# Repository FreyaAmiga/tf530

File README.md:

# TF530

** WARNING THIS IS BETA AT THE MOMENT

This repository contains all the files needed to produce a copy of my accelerator board.

The CPLD Required is a XC9572XL-10VQ64

Everything in this repository is released under the GNU GPLv2. You may create or base commercial PCBs from the work in this repository but you must make the sources for all derivative work available. 

## Firmware / Requirements

  * Xilinx ISE, 14.7 (the final version - other versions may work but this is the one I support)
  * JTAG Adaptor

[For more information visit my channel](https://www.youtube.com/c/TerribleFire)

##License

This project and all the files contained are released under the GNU GPLv2. If you build a modified version of the board you must supply the end user with all the sources (this can be a web link).

##The TerribleFire 530 board (Revision 2)

This board is now in Beta. It may not work in all circumstances but it has been verified to boot AmigaOS 1.3, 2.05 and 3.1 and run various games and desktop apps at 25Mhz. Operation is not guarunteed to be crash free but will work in most "happy path" situations.

I have only verified the HD interface with Compact Flash cards.
I have verified this board boots on Amiga 500 Rev 5, 6a, 8.1a

To buy 10 blank copies of the revision 2 board follow the following link.

http://dirtypcbs.com/store/designer/details/12476/1330/tf530-rev2b-zip

(Terrible Fire gets a $2 "cut" for each order... in reality this is a downpayment on future prototype board orders).

I accept no responsibiltiy for any damage to any equipment that results from the use of this board. IT IS ENTIRELY AT YOUR OWN RISK!

## Installation

Installation is exactly the same as the Kipper2k A508. Refer to http://www.kipper2k.com/a500fastmem.html

You need to connect the OVR and INT2 signals to the A500 header port. 

## What does the board look like

## The BOM 

| Qty | Value           | Device             | Package              | Parts                                                  | Description                   | 
|-----|-----------------|--------------------|----------------------|--------------------------------------------------------|-------------------------------|
| 1   |                 | MC68030RC          | MPGA128              | IC1                                                    | 68xxx PROCESSOR               | 
| 1   |                 | MC68881FN-SOC      | PLCC68-S             | IC2                                                    | 68xxx PROCESSOR               |
| 1   | 10K             | RESISTOR1206       | 1206                 | R3                                                     | Resistors                     |
| 13  | 10uF            | CAP_CERAMIC1206    | 1206                 | C1, C2, C3, C4, C5, C6, C7, C8, C9, C10, C11, C12, C13 | Ceramic Capacitors            | 
| 2   | 47K             | RESISTOR1206       | 1206                 | R1, R2                                                 | Resistors                     | 
| 2   | 74LVC1G17DBV    | 74LVC1G17DBV       | SOT23-5              | IC4, IC5                                               | Single Schmitt-Trigger Buffer | 
| 1   | A500            | JUMPER-2PTH        | 1X02                 | A500                                                   | Jumper                        | 
| 4   | AS7C4096A-12TIN | AS7C4096A-12TCN    | TSOP44-II            | U$1, U$2, U$3, U$4                                     |                               |  
| 1   | AUXPINS         | JUMPER-2PTH        | 1X02                 | AUXPINS                                                | Jumper                        | 
| 1   | BYPASS          | JUMPER-2PTH        | 1X02                 | BYPASS                                                 | Jumper (optional)           | 
| 3   | CAY16-103J4LF   | CAY16-103J4LF      | RESCAXE80P320X160-8N | RN1, RN2, RN3                                          | Res Thick Film Array 10K Ohm  | 
| 1   | CDIS            | JUMPER-2PTH        | 1X02                 | JP5                                                    | Jumper                        |
| 1   | CLOCKSEL        | JUMPER-3PTH        | 1X03                 | JP1                                                    |                               | 
| 1   | EXT5V           | JUMPER-2PTH        | 1X02                 | JP7                                                    | Jumper                        |
| 1   | IDE CONNECTOR   | PINHD-2X20         | 2X20                 | IDE                                                    | PIN HEADER                    |
| 1   | JTAG            | HEADER-1X6ROUND    | 1X06_ROUND           | JTAG                                                   | PIN HEADER                    |
| 1   | LM1117          | V_REG_LM1117SOT223 | SOT223               | U1                                                     | 3.3V Voltage  Regulator LM1117 |
| 1   | MC68000         | MC68000P           | DIL64                | X1                                                     | 68xxx PROCESSOR SOCKET        | 
| 1   | MMUDIS          | JUMPER-2PTH        | 1X02                 | JP3                                                    | Jumper                        | 
| 1   | SPI PORT        | PINHD-2X6          | 2X06                 | SPIPORT                                                | PIN HEADER                    | 
| 1   | X24MHZ          | OSCILLATOR         | OSC_7X5MM            | OSC1                                                   | 24 Mhz llators                   |
| 2   | XC9572XL-10VQ64   | XC9572XL-VQ64      | VQ64                 | XC9572XL(BUS), XC9572XL(RAM)                           |                               |

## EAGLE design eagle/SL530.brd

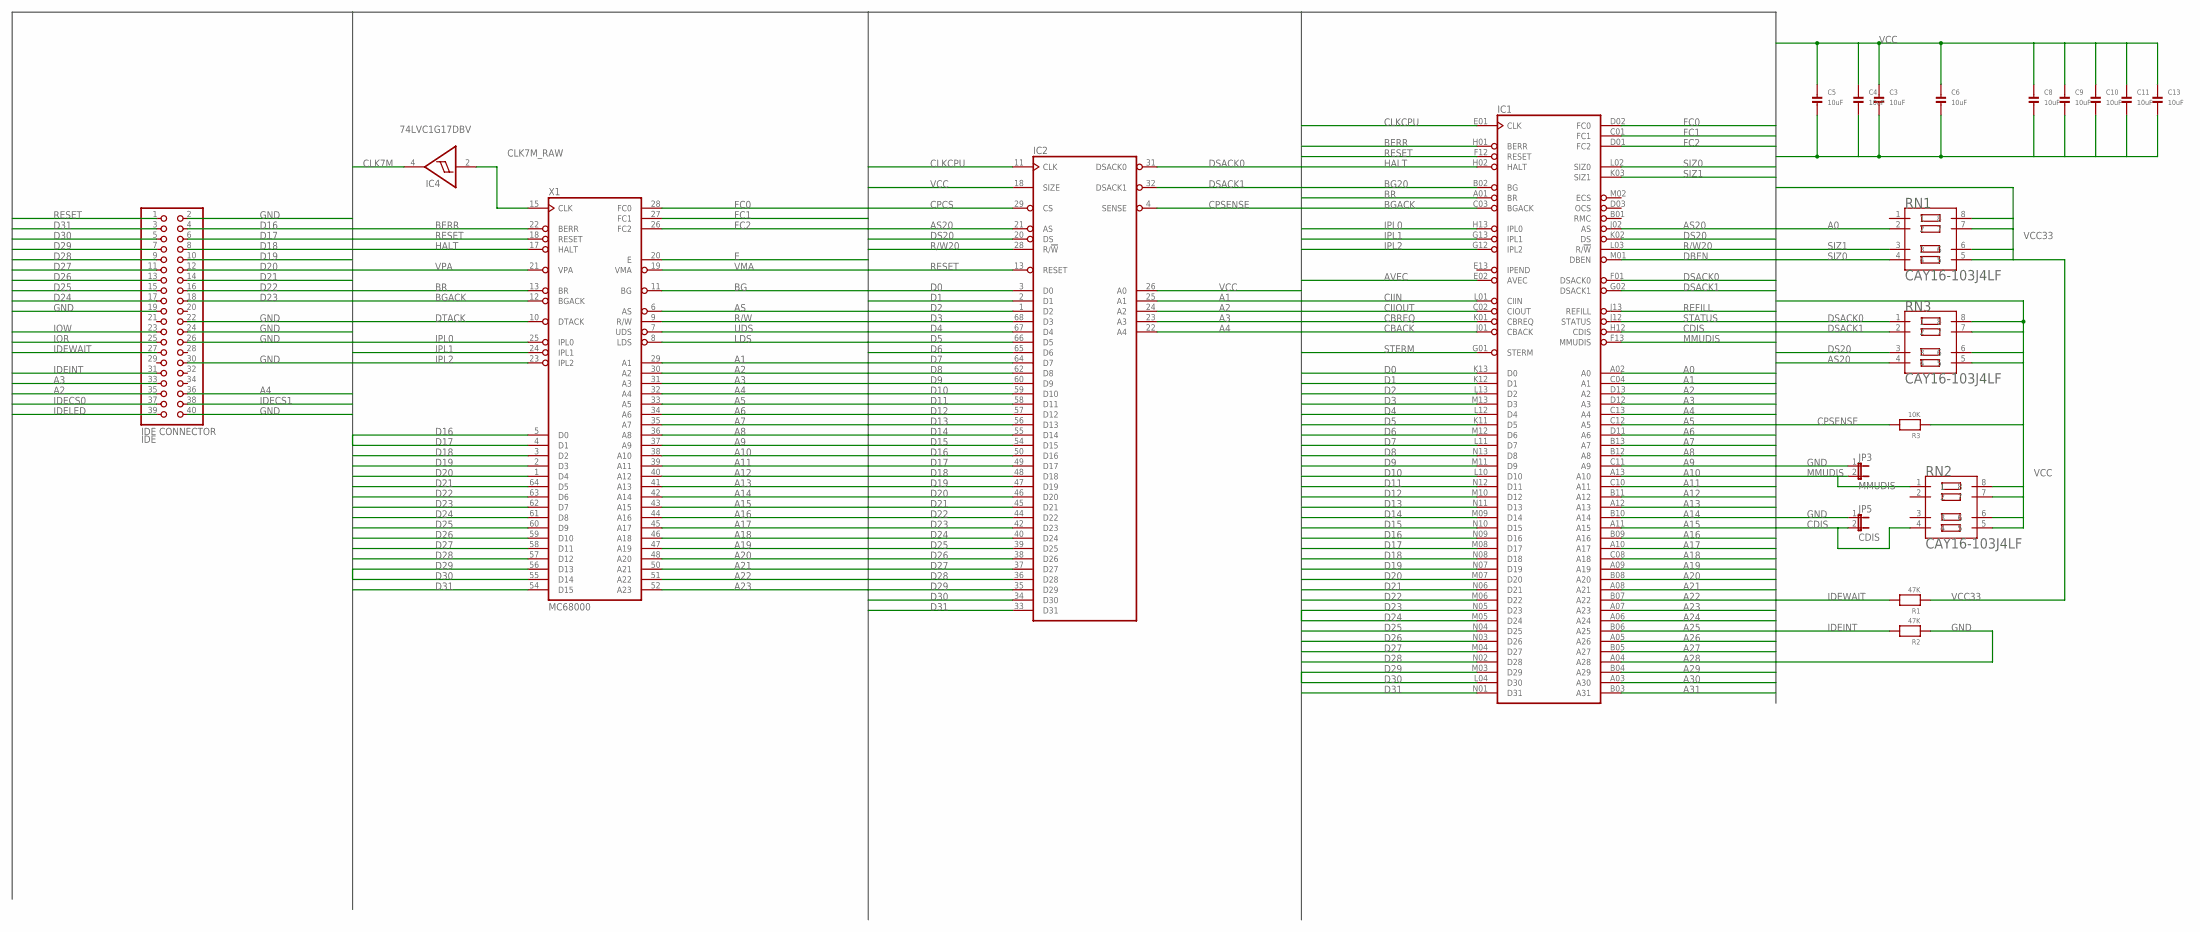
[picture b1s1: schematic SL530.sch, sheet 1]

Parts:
C3, C4, C5, C6, C8, C9, C10, C11, C13: 10uF; 1206
IC1: MC68030RC; MPGA128
IC2: MC68881FN-SOC; PLCC68-S
IC4: 74LVC1G17DBV; SOT23-5
IDE: IDE CONNECTOR; 2X20
JP3: MMUDIS; 1X02
JP5: CDIS; 1X02
R1, R2: 47K; 1206
R3: 10K; 1206
RN1, RN2, RN3: CAY16-103J4LF; RESCAXE80P320X160-8N
X1: MC68000; DIL64

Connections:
A0: IC1.A02 (A0), RN1.2; also elsewhere on the board
A1: IC1.C04 (A1), IC2.25 (A1), X1.29 (A1); also elsewhere on the board
A2: IC1.D13 (A2), IC2.24 (A2), IDE.35, X1.30 (A2); also elsewhere on the board
A3: IC1.D12 (A3), IC2.23 (A3), IDE.33, X1.31 (A3); also elsewhere on the board
A4: IC1.C13 (A4), IC2.22 (A4), IDE.36, X1.32 (A4); also elsewhere on the board
A5: IC1.C12 (A5), X1.33 (A5); also elsewhere on the board
A6: IC1.D11 (A6), X1.34 (A6); also elsewhere on the board
A7: IC1.B13 (A7), X1.35 (A7); also elsewhere on the board
A8: IC1.B12 (A8), X1.36 (A8); also elsewhere on the board
A9: IC1.C11 (A9), X1.37 (A9); also elsewhere on the board
A10: IC1.A13 (A10), X1.38 (A10); also elsewhere on the board
A11: IC1.C10 (A11), X1.39 (A11); also elsewhere on the board
A12: IC1.B11 (A12), X1.40 (A12); also elsewhere on the board
A13: IC1.A12 (A13), X1.41 (A13); also elsewhere on the board
A14: IC1.B10 (A14), X1.42 (A14); also elsewhere on the board
A15: IC1.A11 (A15), X1.43 (A15); also elsewhere on the board
A16: IC1.B09 (A16), X1.44 (A16); also elsewhere on the board
A17: IC1.A10 (A17), X1.45 (A17); also elsewhere on the board
A18: IC1.C08 (A18), X1.46 (A18); also elsewhere on the board
A19: IC1.A09 (A19), X1.47 (A19); also elsewhere on the board
A20: IC1.B08 (A20), X1.48 (A20); also elsewhere on the board
A21: IC1.A08 (A21), X1.50 (A21); also elsewhere on the board
A22: IC1.B07 (A22), X1.51 (A22); also elsewhere on the board
A23: IC1.A07 (A23), X1.52 (A23); also elsewhere on the board
A24: IC1.A06 (A24)
A25: IC1.B06 (A25)
A26: IC1.A05 (A26)
A27: IC1.B05 (A27)
A28: IC1.A04 (A28)
A29: IC1.B04 (A29)
A30: IC1.A03 (A30)
A31: IC1.B03 (A31)
AS: X1.6 (AS); also elsewhere on the board
AS20: IC1.J02 (AS), IC2.21 (AS), RN3.4; also elsewhere on the board
AVEC: IC1.E02 (AVEC); also elsewhere on the board
BERR: IC1.H01 (BERR), X1.22 (BERR); also elsewhere on the board
BG: X1.11 (BG); also elsewhere on the board
BG20: IC1.B02 (BG); also elsewhere on the board
BGACK: IC1.C03 (BGACK), X1.12 (BGACK); also elsewhere on the board
BR: IC1.A01 (BR), X1.13 (BR)
CBACK: IC1.J01 (CBACK); also elsewhere on the board
CBREQ: IC1.K01 (CBREQ); also elsewhere on the board
CDIS: IC1.H12 (CDIS), JP5.2, RN2.4
CIIN: IC1.L01 (CIIN); also elsewhere on the board
CIIOUT: IC1.C02 (CIOUT)
CLK7M: IC4.4 (O); also elsewhere on the board
CLK7M_RAW: IC4.2 (I), X1.15 (CLK)
CLKCPU: IC1.E01 (CLK), IC2.11 (CLK); also elsewhere on the board
CPCS: IC2.29 (CS); also elsewhere on the board
CPSENSE: IC2.4 (SENSE), R3.2; also elsewhere on the board
D0: IC1.K13 (D0), IC2.3 (D0); also elsewhere on the board
D1: IC1.K12 (D1), IC2.2 (D1); also elsewhere on the board
D2: IC1.L13 (D2), IC2.1 (D2); also elsewhere on the board
D3: IC1.M13 (D3), IC2.68 (D3); also elsewhere on the board
D4: IC1.L12 (D4), IC2.67 (D4); also elsewhere on the board
D5: IC1.K11 (D5), IC2.66 (D5); also elsewhere on the board
D6: IC1.M12 (D6), IC2.65 (D6); also elsewhere on the board
D7: IC1.L11 (D7), IC2.64 (D7); also elsewhere on the board
D8: IC1.N13 (D8), IC2.62 (D8); also elsewhere on the board
D9: IC1.M11 (D9), IC2.60 (D9); also elsewhere on the board
D10: IC1.L10 (D10), IC2.59 (D10); also elsewhere on the board
D11: IC1.N12 (D11), IC2.58 (D11); also elsewhere on the board
D12: IC1.M10 (D12), IC2.57 (D12); also elsewhere on the board
D13: IC1.N11 (D13), IC2.56 (D13); also elsewhere on the board
D14: IC1.M09 (D14), IC2.55 (D14); also elsewhere on the board
D15: IC1.N10 (D15), IC2.54 (D15); also elsewhere on the board
D16: IC1.N09 (D16), IC2.50 (D16), IDE.4, X1.5 (D0); also elsewhere on the board
D17: IC1.M08 (D17), IC2.49 (D17), IDE.6, X1.4 (D1); also elsewhere on the board
D18: IC1.N08 (D18), IC2.48 (D18), IDE.8, X1.3 (D2); also elsewhere on the board
D19: IC1.N07 (D19), IC2.47 (D19), IDE.10, X1.2 (D3); also elsewhere on the board
D20: IC1.M07 (D20), IC2.46 (D20), IDE.12, X1.1 (D4); also elsewhere on the board
D21: IC1.N06 (D21), IC2.45 (D21), IDE.14, X1.64 (D5); also elsewhere on the board
D22: IC1.M06 (D22), IC2.44 (D22), IDE.16, X1.63 (D6); also elsewhere on the board
D23: IC1.N05 (D23), IC2.42 (D23), IDE.18, X1.62 (D7); also elsewhere on the board
D24: IC1.M05 (D24), IC2.40 (D24), IDE.17, X1.61 (D8); also elsewhere on the board
D25: IC1.N04 (D25), IC2.39 (D25), IDE.15, X1.60 (D9); also elsewhere on the board
D26: IC1.N03 (D26), IC2.38 (D26), IDE.13, X1.59 (D10); also elsewhere on the board
D27: IC1.M04 (D27), IC2.37 (D27), IDE.11, X1.58 (D11); also elsewhere on the board
D28: IC1.N02 (D28), IC2.36 (D28), IDE.9, X1.57 (D12); also elsewhere on the board
D29: IC1.M03 (D29), IC2.35 (D29), IDE.7, X1.56 (D13); also elsewhere on the board
D30: IC1.L04 (D30), IC2.34 (D30), IDE.5, X1.55 (D14); also elsewhere on the board
D31: IC1.N01 (D31), IC2.33 (D31), IDE.3, X1.54 (D15); also elsewhere on the board
DBEN: IC1.M01 (DBEN)
DS20: IC1.K02 (DS), IC2.20 (DS), RN3.3; also elsewhere on the board
DSACK0: IC1.F01 (DSACK0), IC2.31 (DSACK0), RN3.1; also elsewhere on the board
DSACK1: IC1.G02 (DSACK1), IC2.32 (DSACK1), RN3.2; also elsewhere on the board
DTACK: X1.10 (DTACK); also elsewhere on the board
E: X1.20 (E); also elsewhere on the board
FC0: IC1.D02 (FC0), X1.28 (FC0); also elsewhere on the board
FC1: IC1.C01 (FC1), X1.27 (FC1); also elsewhere on the board
FC2: IC1.D01 (FC2), X1.26 (FC2); also elsewhere on the board
GND: C3.2, C4.2, C5.2, C6.2, C8.2, C9.2, C10.2, C11.2, C13.2, IC1.C05 (GND), IC1.C07 (GND), IC1.C09 (GND), IC1.E03 (GND), IC1.E11 (GND), IC1.F03 (GND), IC1.G03 (GND), IC1.G11 (GND), IC1.J03 (GND), IC1.J11 (GND), IC1.L05 (GND), IC1.L07 (GND), IC1.L08 (GND), IC1.L09 (GND), IC2.5 (GND), IC2.6 (GND), IC2.7 (GND), IC2.8 (GND), IC2.9 (GND), IC2.12 (GND), IC2.14 (GND), IC2.19 (GND), IC2.30 (GND), IC2.41 (GND), IC2.51 (GND), IC2.63 (GND), IC4.3 (GND), IDE.2, IDE.19, IDE.22, IDE.24, IDE.26, IDE.30, IDE.40, JP3.1, JP5.1, R2.1, X1.16 (GND), X1.53 (GND); also elsewhere on the board
HALT: IC1.H02 (HALT), X1.17 (HALT); also elsewhere on the board
IDECS0: IDE.37; also elsewhere on the board
IDECS1: IDE.38; also elsewhere on the board
IDEINT: IDE.31, R2.2; also elsewhere on the board
IDELED: IDE.39
IDEWAIT: IDE.27, R1.2; also elsewhere on the board
IOR: IDE.25; also elsewhere on the board
IOW: IDE.23; also elsewhere on the board
IPL0: IC1.H13 (IPL0), X1.25 (IPL0)
IPL1: IC1.G13 (IPL1), X1.24 (IPL1)
IPL2: IC1.G12 (IPL2), X1.23 (IPL2)
LDS: X1.8 (LDS); also elsewhere on the board
MMUDIS: IC1.F13 (MMUDIS), JP3.2, RN2.1
R/W: X1.9 (R/W); also elsewhere on the board
R/W20: IC1.L03 (R/!W), IC2.28 (R/!W); also elsewhere on the board
REFILL: IC1.J13 (REFILL)
RESET: IC1.F12 (RESET), IC2.13 (RESET), IDE.1, X1.18 (RESET); also elsewhere on the board
SIZ0: IC1.L02 (SIZ0), RN1.4; also elsewhere on the board
SIZ1: IC1.K03 (SIZ1), RN1.3; also elsewhere on the board
STATUS: IC1.J12 (STATUS)
STERM: IC1.G01 (STERM); also elsewhere on the board
UDS: X1.7 (UDS); also elsewhere on the board
VCC: C3.1, C4.1, C5.1, C6.1, C8.1, C9.1, C10.1, C11.1, C13.1, IC1.C06 (VCC), IC1.D04 (VCC), IC1.D10 (VCC), IC1.F02 (VCC), IC1.F11 (VCC), IC1.H03 (VCC), IC1.H11 (VCC), IC1.K04 (VCC), IC1.K10 (VCC), IC1.L06 (VCC), IC2.10 (VCC), IC2.16 (VCC), IC2.17 (VCC), IC2.18 (SIZE), IC2.26 (A0), IC2.27 (VCC), IC2.43 (VCC), IC2.52 (VCC), IC2.53 (VCC), IC2.61 (VCC), IC4.5 (VCC), R3.1, RN2.5, RN2.6, RN2.7, RN2.8, RN3.5, RN3.6, RN3.7, RN3.8, X1.14 (VCC), X1.49 (VCC); also elsewhere on the board
VCC33: R1.1, RN1.5, RN1.6, RN1.7, RN1.8; also elsewhere on the board
VMA: X1.19 (VMA); also elsewhere on the board
VPA: X1.21 (VPA); also elsewhere on the board

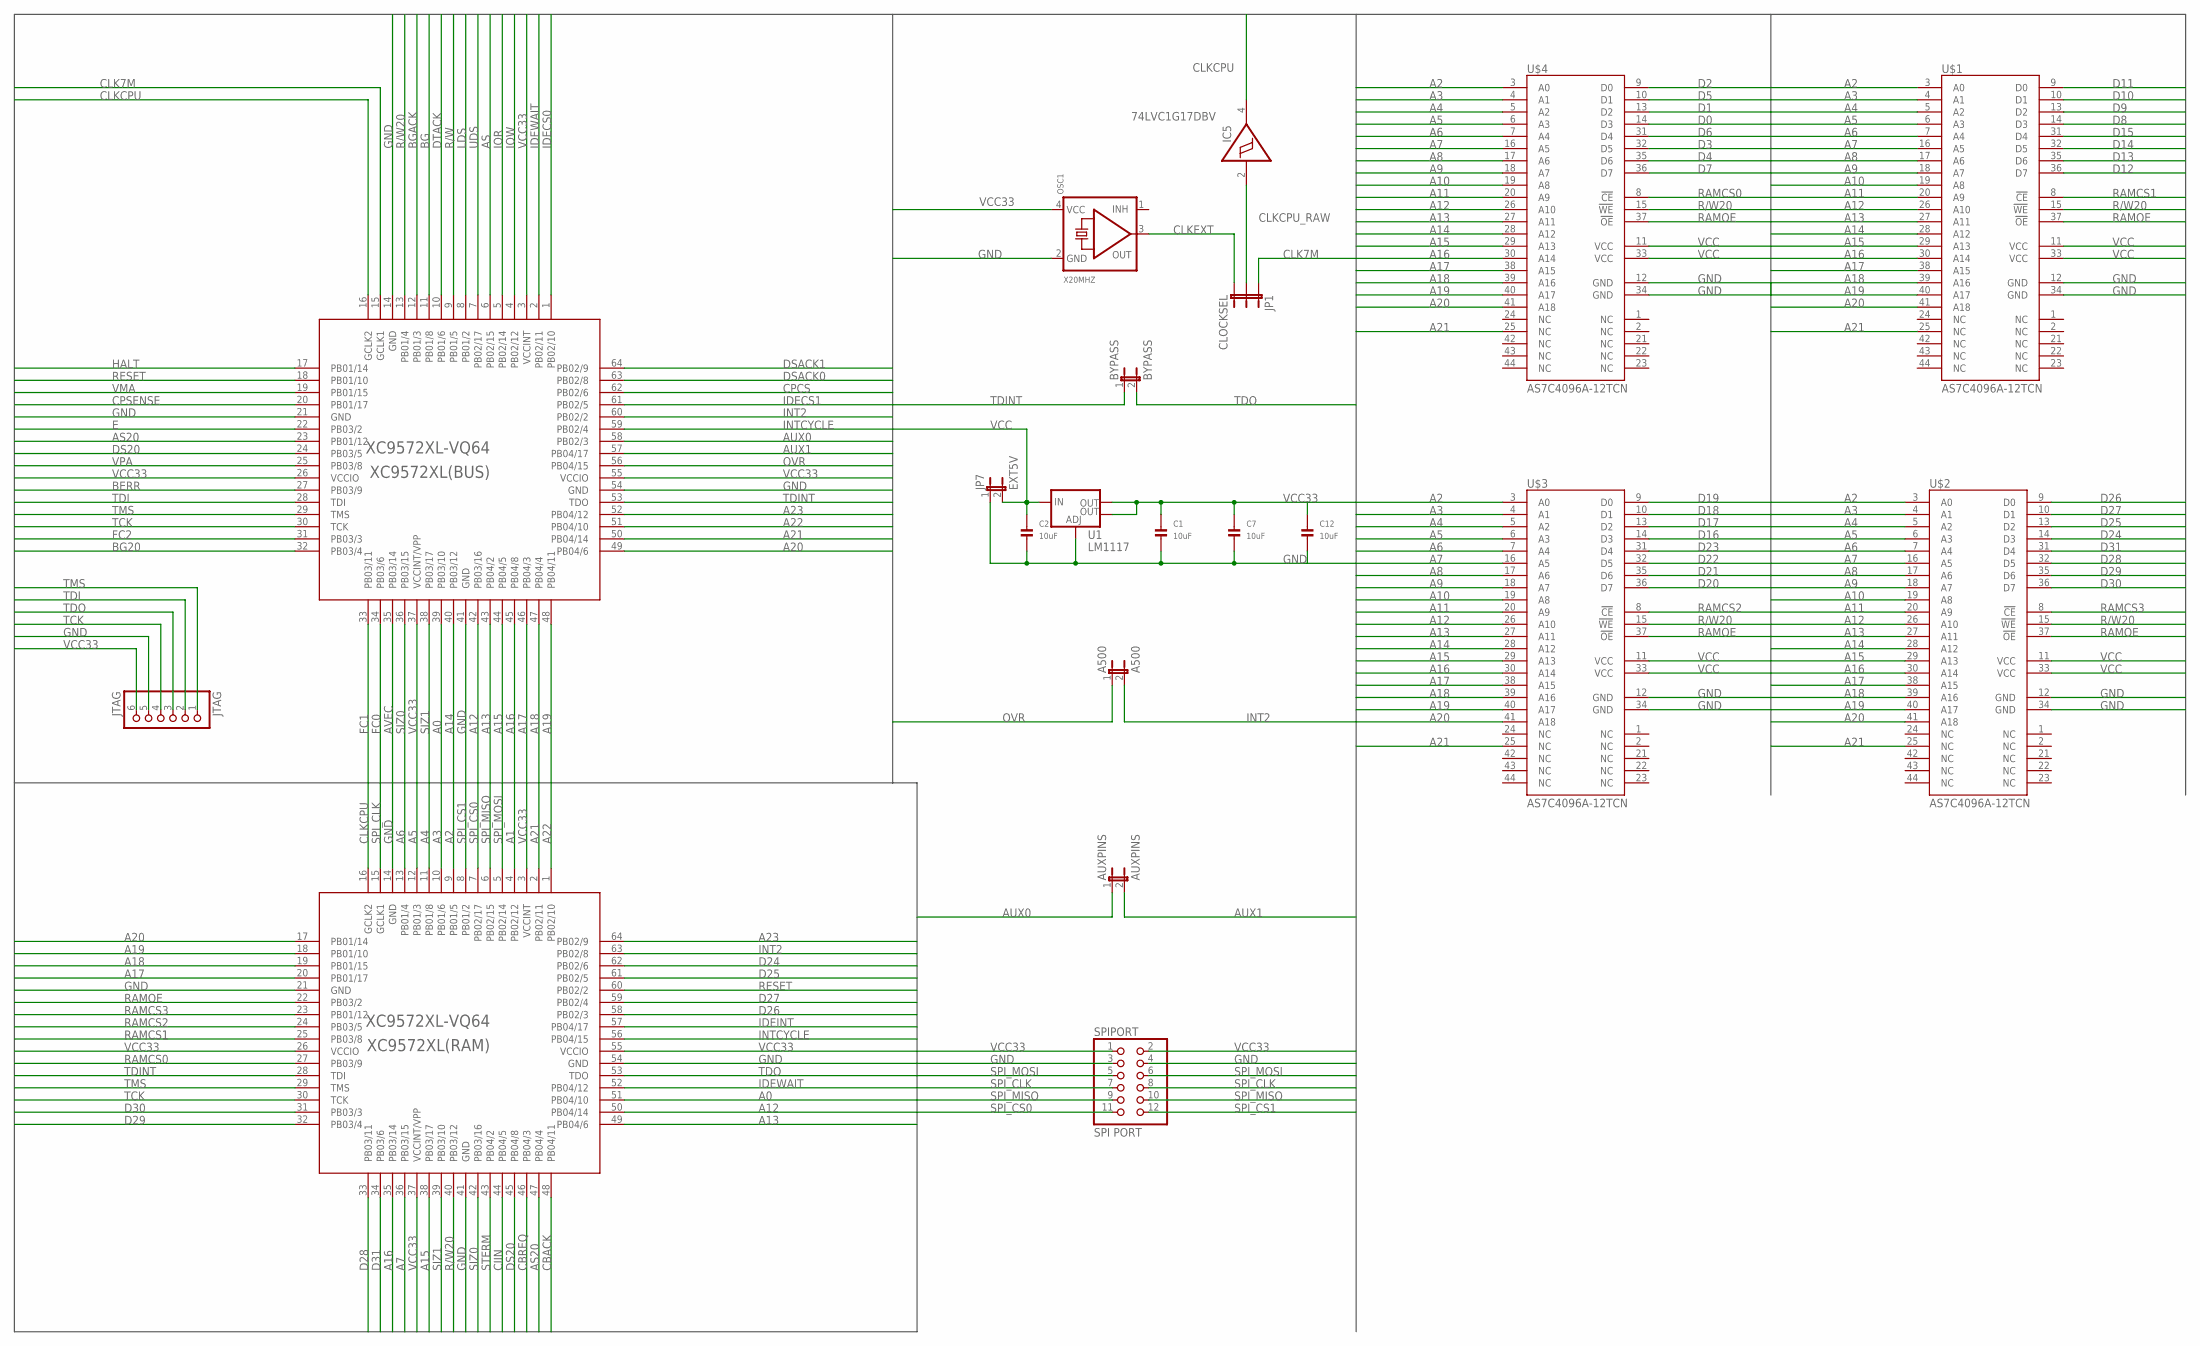
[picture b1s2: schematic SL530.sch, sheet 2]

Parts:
A500: A500; 1X02
AUXPINS: AUXPINS; 1X02
BYPASS: BYPASS; 1X02
C1, C2, C7, C12: 10uF; 1206
IC5: 74LVC1G17DBV; SOT23-5
JP1: CLOCKSEL; 1X03
JP7: EXT5V; 1X02
JTAG: JTAG; 1X06_ROUND
OSC1: X20MHZ; OSC_7X5MM
SPIPORT: SPI PORT; 2X06
U1: LM1117; SOT223
U$1, U$2, U$3, U$4: AS7C4096A-12TCN; TSOP44-II
XC9572XL(BUS), XC9572XL(RAM): XC9572XL-VQ64; VQ64

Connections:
A0: XC9572XL(BUS).39 (PB03/10), XC9572XL(RAM).51 (PB04/10); also elsewhere on the board
A1: XC9572XL(RAM).4 (PB02/12); also elsewhere on the board
A2: U$1.3 (A0), U$2.3 (A0), U$3.3 (A0), U$4.3 (A0), XC9572XL(RAM).9 (PB01/5); also elsewhere on the board
A3: U$1.4 (A1), U$2.4 (A1), U$3.4 (A1), U$4.4 (A1), XC9572XL(RAM).10 (PB01/6); also elsewhere on the board
A4: U$1.5 (A2), U$2.5 (A2), U$3.5 (A2), U$4.5 (A2), XC9572XL(RAM).11 (PB01/8); also elsewhere on the board
A5: U$1.6 (A3), U$2.6 (A3), U$3.6 (A3), U$4.6 (A3), XC9572XL(RAM).12 (PB01/3); also elsewhere on the board
A6: U$1.7 (A4), U$2.7 (A4), U$3.7 (A4), U$4.7 (A4), XC9572XL(RAM).13 (PB01/4); also elsewhere on the board
A7: U$1.16 (A5), U$2.16 (A5), U$3.16 (A5), U$4.16 (A5), XC9572XL(RAM).36 (PB03/15); also elsewhere on the board
A8: U$1.17 (A6), U$2.17 (A6), U$3.17 (A6), U$4.17 (A6); also elsewhere on the board
A9: U$1.18 (A7), U$2.18 (A7), U$3.18 (A7), U$4.18 (A7); also elsewhere on the board
A10: U$1.19 (A8), U$2.19 (A8), U$3.19 (A8), U$4.19 (A8); also elsewhere on the board
A11: U$1.20 (A9), U$2.20 (A9), U$3.20 (A9), U$4.20 (A9); also elsewhere on the board
A12: U$1.26 (A10), U$2.26 (A10), U$3.26 (A10), U$4.26 (A10), XC9572XL(BUS).42 (PB03/16), XC9572XL(RAM).50 (PB04/14); also elsewhere on the board
A13: U$1.27 (A11), U$2.27 (A11), U$3.27 (A11), U$4.27 (A11), XC9572XL(BUS).43 (PB04/2), XC9572XL(RAM).49 (PB04/6); also elsewhere on the board
A14: U$1.28 (A12), U$2.28 (A12), U$3.28 (A12), U$4.28 (A12), XC9572XL(BUS).40 (PB03/12); also elsewhere on the board
A15: U$1.29 (A13), U$2.29 (A13), U$3.29 (A13), U$4.29 (A13), XC9572XL(BUS).44 (PB04/5), XC9572XL(RAM).38 (PB03/17); also elsewhere on the board
A16: U$1.30 (A14), U$2.30 (A14), U$3.30 (A14), U$4.30 (A14), XC9572XL(BUS).45 (PB04/8), XC9572XL(RAM).35 (PB03/14); also elsewhere on the board
A17: U$1.38 (A15), U$2.38 (A15), U$3.38 (A15), U$4.38 (A15), XC9572XL(BUS).46 (PB04/3), XC9572XL(RAM).20 (PB01/17); also elsewhere on the board
A18: U$1.39 (A16), U$2.39 (A16), U$3.39 (A16), U$4.39 (A16), XC9572XL(BUS).47 (PB04/4), XC9572XL(RAM).19 (PB01/15); also elsewhere on the board
A19: U$1.40 (A17), U$2.40 (A17), U$3.40 (A17), U$4.40 (A17), XC9572XL(BUS).48 (PB04/11), XC9572XL(RAM).18 (PB01/10); also elsewhere on the board
A20: U$1.41 (A18), U$2.41 (A18), U$3.41 (A18), U$4.41 (A18), XC9572XL(BUS).49 (PB04/6), XC9572XL(RAM).17 (PB01/14); also elsewhere on the board
A21: U$1.25 (NC), U$2.25 (NC), U$3.25 (NC), U$4.25 (NC), XC9572XL(BUS).50 (PB04/14), XC9572XL(RAM).2 (PB02/11); also elsewhere on the board
A22: XC9572XL(BUS).51 (PB04/10), XC9572XL(RAM).1 (PB02/10); also elsewhere on the board
A23: XC9572XL(BUS).52 (PB04/12), XC9572XL(RAM).64 (PB02/9); also elsewhere on the board
AS: XC9572XL(BUS).6 (PB02/15); also elsewhere on the board
AS20: XC9572XL(BUS).23 (PB01/12), XC9572XL(RAM).47 (PB04/4); also elsewhere on the board
AUX0: AUXPINS.1, XC9572XL(BUS).58 (PB02/3)
AUX1: AUXPINS.2, XC9572XL(BUS).57 (PB04/17)
AVEC: XC9572XL(BUS).35 (PB03/14); also elsewhere on the board
BERR: XC9572XL(BUS).27 (PB03/9); also elsewhere on the board
BG: XC9572XL(BUS).11 (PB01/8); also elsewhere on the board
BG20: XC9572XL(BUS).32 (PB03/4); also elsewhere on the board
BGACK: XC9572XL(BUS).12 (PB01/3); also elsewhere on the board
CBACK: XC9572XL(RAM).48 (PB04/11); also elsewhere on the board
CBREQ: XC9572XL(RAM).46 (PB04/3); also elsewhere on the board
CIIN: XC9572XL(RAM).44 (PB04/5); also elsewhere on the board
CLK7M: JP1.1, XC9572XL(BUS).15 (GCLK1); also elsewhere on the board
CLKCPU: IC5.4 (O), XC9572XL(BUS).16 (GCLK2), XC9572XL(RAM).16 (GCLK2); also elsewhere on the board
CLKCPU_RAW: IC5.2 (I), JP1.2
CLKEXT: JP1.3, OSC1.3 (OUT)
CPCS: XC9572XL(BUS).62 (PB02/6); also elsewhere on the board
CPSENSE: XC9572XL(BUS).20 (PB01/17); also elsewhere on the board
D0: U$4.14 (D3); also elsewhere on the board
D1: U$4.13 (D2); also elsewhere on the board
D2: U$4.9 (D0); also elsewhere on the board
D3: U$4.32 (D5); also elsewhere on the board
D4: U$4.35 (D6); also elsewhere on the board
D5: U$4.10 (D1); also elsewhere on the board
D6: U$4.31 (D4); also elsewhere on the board
D7: U$4.36 (D7); also elsewhere on the board
D8: U$1.14 (D3); also elsewhere on the board
D9: U$1.13 (D2); also elsewhere on the board
D10: U$1.10 (D1); also elsewhere on the board
D11: U$1.9 (D0); also elsewhere on the board
D12: U$1.36 (D7); also elsewhere on the board
D13: U$1.35 (D6); also elsewhere on the board
D14: U$1.32 (D5); also elsewhere on the board
D15: U$1.31 (D4); also elsewhere on the board
D16: U$3.14 (D3); also elsewhere on the board
D17: U$3.13 (D2); also elsewhere on the board
D18: U$3.10 (D1); also elsewhere on the board
D19: U$3.9 (D0); also elsewhere on the board
D20: U$3.36 (D7); also elsewhere on the board
D21: U$3.35 (D6); also elsewhere on the board
D22: U$3.32 (D5); also elsewhere on the board
D23: U$3.31 (D4); also elsewhere on the board
D24: U$2.14 (D3), XC9572XL(RAM).62 (PB02/6); also elsewhere on the board
D25: U$2.13 (D2), XC9572XL(RAM).61 (PB02/5); also elsewhere on the board
D26: U$2.9 (D0), XC9572XL(RAM).58 (PB02/3); also elsewhere on the board
D27: U$2.10 (D1), XC9572XL(RAM).59 (PB02/4); also elsewhere on the board
D28: U$2.32 (D5), XC9572XL(RAM).33 (PB03/11); also elsewhere on the board
D29: U$2.35 (D6), XC9572XL(RAM).32 (PB03/4); also elsewhere on the board
D30: U$2.36 (D7), XC9572XL(RAM).31 (PB03/3); also elsewhere on the board
D31: U$2.31 (D4), XC9572XL(RAM).34 (PB03/6); also elsewhere on the board
DS20: XC9572XL(BUS).24 (PB03/5), XC9572XL(RAM).45 (PB04/8); also elsewhere on the board
DSACK0: XC9572XL(BUS).63 (PB02/8); also elsewhere on the board
DSACK1: XC9572XL(BUS).64 (PB02/9); also elsewhere on the board
DTACK: XC9572XL(BUS).10 (PB01/6); also elsewhere on the board
E: XC9572XL(BUS).22 (PB03/2); also elsewhere on the board
FC0: XC9572XL(BUS).34 (PB03/6); also elsewhere on the board
FC1: XC9572XL(BUS).33 (PB03/11); also elsewhere on the board
FC2: XC9572XL(BUS).31 (PB03/3); also elsewhere on the board
GND: C1.2, C2.2, C7.2, C12.2, IC5.3 (GND), JP7.1, JTAG.5, OSC1.2 (GND), SPIPORT.3, SPIPORT.4, U1.1 (ADJ), U$1.12 (GND), U$1.34 (GND), U$2.12 (GND), U$2.34 (GND), U$3.12 (GND), U$3.34 (GND), U$4.12 (GND), U$4.34 (GND), XC9572XL(BUS).14 (GND), XC9572XL(BUS).21 (GND), XC9572XL(BUS).41 (GND), XC9572XL(BUS).54 (GND), XC9572XL(RAM).14 (GND), XC9572XL(RAM).21 (GND), XC9572XL(RAM).41 (GND), XC9572XL(RAM).54 (GND); also elsewhere on the board
HALT: XC9572XL(BUS).17 (PB01/14); also elsewhere on the board
IDECS0: XC9572XL(BUS).1 (PB02/10); also elsewhere on the board
IDECS1: XC9572XL(BUS).61 (PB02/5); also elsewhere on the board
IDEINT: XC9572XL(RAM).57 (PB04/17); also elsewhere on the board
IDEWAIT: XC9572XL(BUS).2 (PB02/11), XC9572XL(RAM).52 (PB04/12); also elsewhere on the board
INT2: A500.2, XC9572XL(BUS).60 (PB02/2), XC9572XL(RAM).63 (PB02/8)
INTCYCLE: XC9572XL(BUS).59 (PB02/4), XC9572XL(RAM).56 (PB04/15)
IOR: XC9572XL(BUS).5 (PB02/14); also elsewhere on the board
IOW: XC9572XL(BUS).4 (PB02/12); also elsewhere on the board
LDS: XC9572XL(BUS).8 (PB01/2); also elsewhere on the board
OVR: A500.1, XC9572XL(BUS).56 (PB04/15)
R/W: XC9572XL(BUS).9 (PB01/5); also elsewhere on the board
R/W20: U$1.15 (!WE), U$2.15 (!WE), U$3.15 (!WE), U$4.15 (!WE), XC9572XL(BUS).13 (PB01/4), XC9572XL(RAM).40 (PB03/12); also elsewhere on the board
RAMCS0: U$4.8 (!CE), XC9572XL(RAM).27 (PB03/9)
RAMCS1: U$1.8 (!CE), XC9572XL(RAM).25 (PB03/8)
RAMCS2: U$3.8 (!CE), XC9572XL(RAM).24 (PB03/5)
RAMCS3: U$2.8 (!CE), XC9572XL(RAM).23 (PB01/12)
RAMOE: U$1.37 (!OE), U$2.37 (!OE), U$3.37 (!OE), U$4.37 (!OE), XC9572XL(RAM).22 (PB03/2)
RESET: XC9572XL(BUS).18 (PB01/10), XC9572XL(RAM).60 (PB02/2); also elsewhere on the board
SIZ0: XC9572XL(BUS).36 (PB03/15), XC9572XL(RAM).42 (PB03/16); also elsewhere on the board
SIZ1: XC9572XL(BUS).38 (PB03/17), XC9572XL(RAM).39 (PB03/10); also elsewhere on the board
SPI_CLK: SPIPORT.7, SPIPORT.8, XC9572XL(RAM).15 (GCLK1)
SPI_CS0: SPIPORT.11, XC9572XL(RAM).7 (PB02/17)
SPI_CS1: SPIPORT.12, XC9572XL(RAM).8 (PB01/2)
SPI_MISO: SPIPORT.9, SPIPORT.10, XC9572XL(RAM).6 (PB02/15)
SPI_MOSI: SPIPORT.5, SPIPORT.6, XC9572XL(RAM).5 (PB02/14)
STERM: XC9572XL(RAM).43 (PB04/2); also elsewhere on the board
TCK: JTAG.4, XC9572XL(BUS).30 (TCK), XC9572XL(RAM).30 (TCK)
TDI: JTAG.2, XC9572XL(BUS).28 (TDI)
TDINT: BYPASS.1, XC9572XL(BUS).53 (TDO), XC9572XL(RAM).28 (TDI)
TDO: BYPASS.2, JTAG.3, XC9572XL(RAM).53 (TDO)
TMS: JTAG.1, XC9572XL(BUS).29 (TMS), XC9572XL(RAM).29 (TMS)
UDS: XC9572XL(BUS).7 (PB02/17); also elsewhere on the board
VCC: C2.1, IC5.5 (VCC), JP7.2, U1.3 (IN), U$1.11 (VCC), U$1.33 (VCC), U$2.11 (VCC), U$2.33 (VCC), U$3.11 (VCC), U$3.33 (VCC), U$4.11 (VCC), U$4.33 (VCC); also elsewhere on the board
VCC33: C1.1, C7.1, C12.1, JTAG.6, OSC1.4 (VCC), SPIPORT.1, SPIPORT.2, U1.2 (OUT), U1.4 (OUT), XC9572XL(BUS).3 (VCCINT), XC9572XL(BUS).26 (VCCIO), XC9572XL(BUS).37 (VCCINT/VPP), XC9572XL(BUS).55 (VCCIO), XC9572XL(RAM).3 (VCCINT), XC9572XL(RAM).26 (VCCIO), XC9572XL(RAM).37 (VCCINT/VPP), XC9572XL(RAM).55 (VCCIO); also elsewhere on the board
VMA: XC9572XL(BUS).19 (PB01/15); also elsewhere on the board
VPA: XC9572XL(BUS).25 (PB03/8); also elsewhere on the board

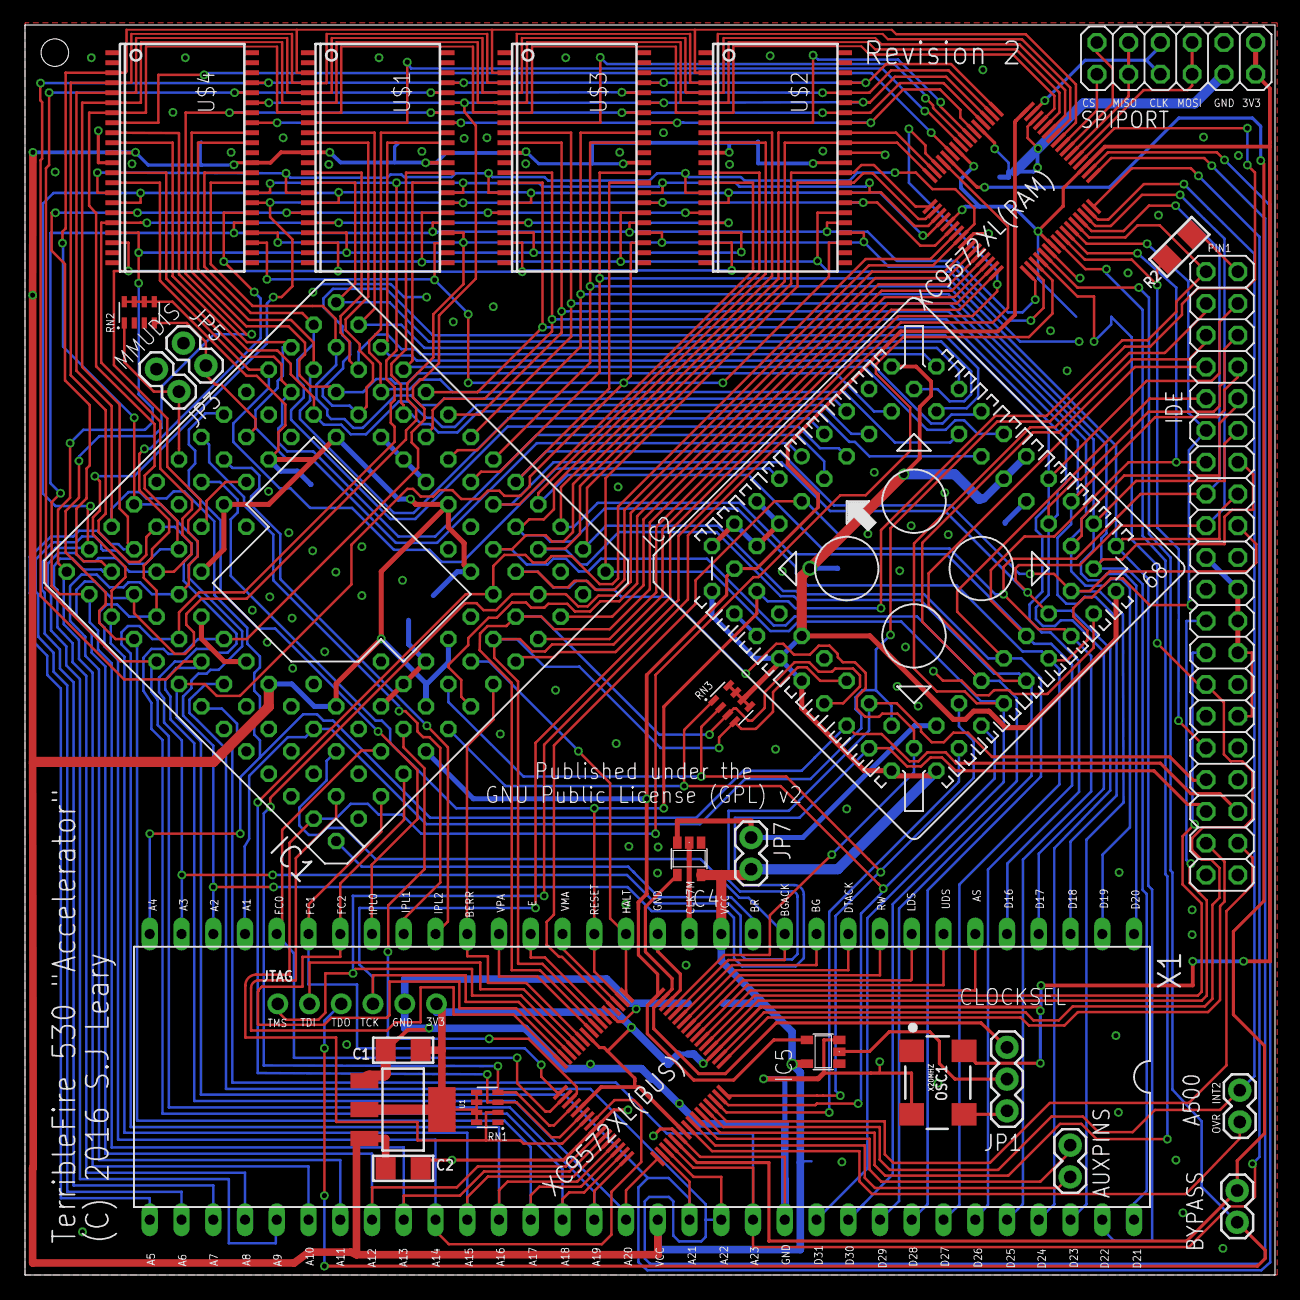
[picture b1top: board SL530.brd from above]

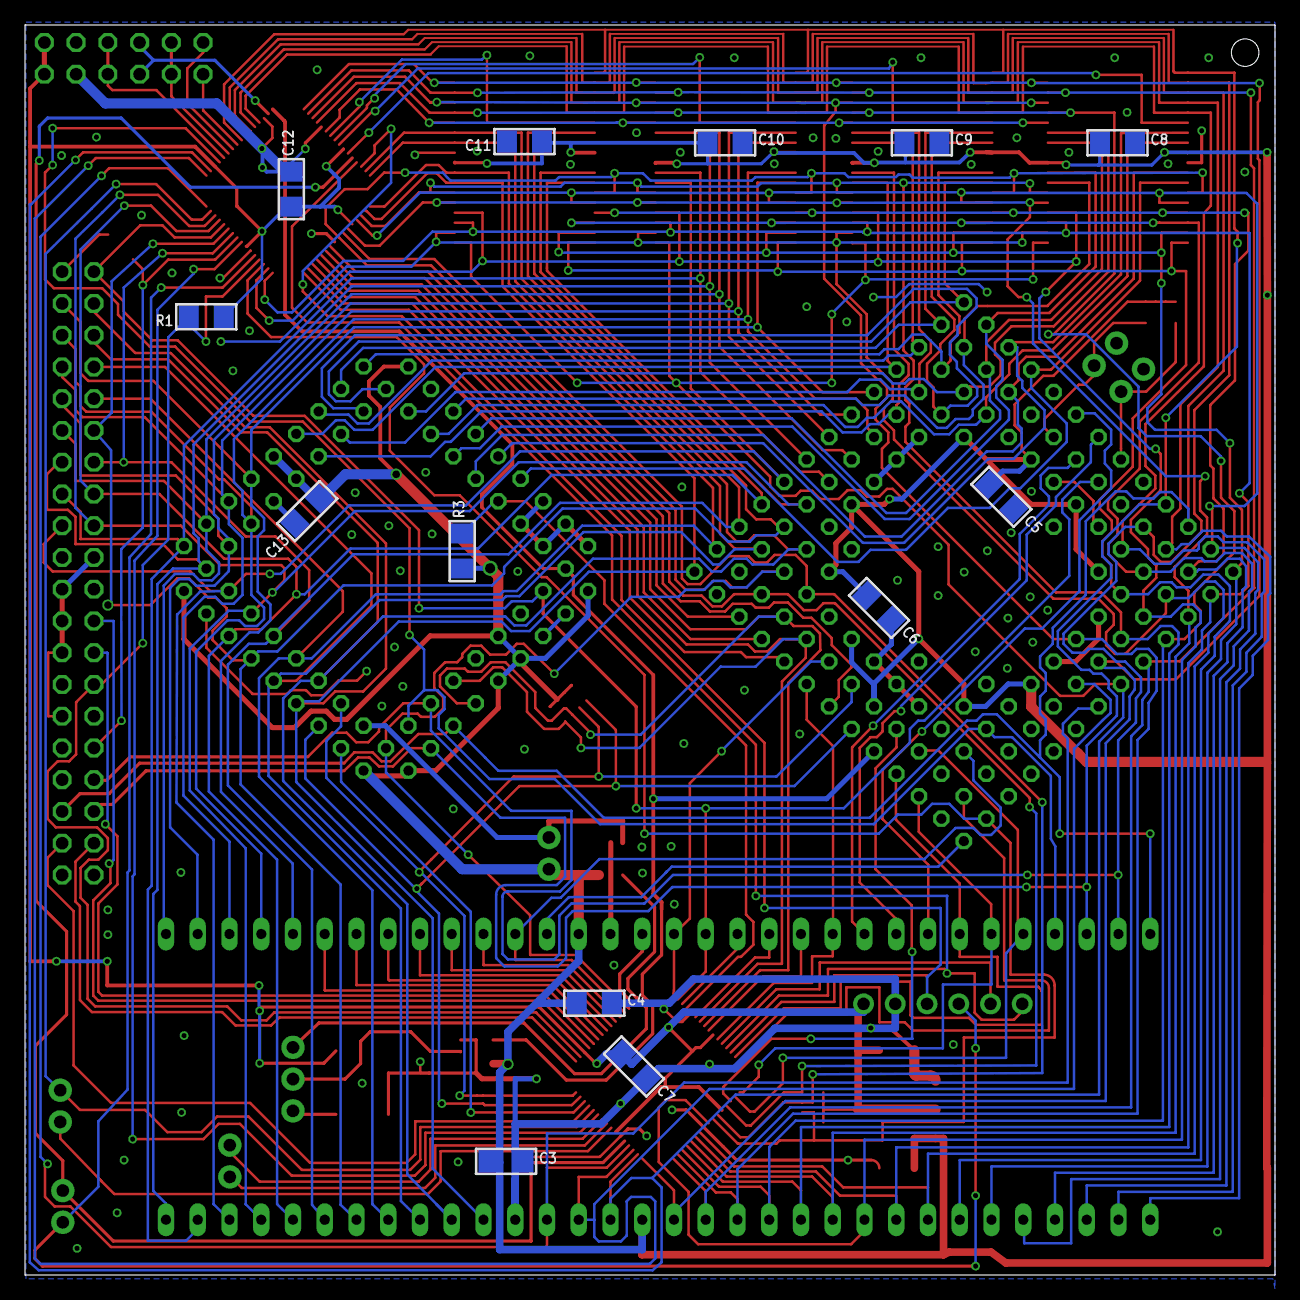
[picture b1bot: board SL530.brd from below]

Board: 2 copper layers, 100.0 x 100.0 mm, 42 parts (13 on the bottom side), 127 nets.

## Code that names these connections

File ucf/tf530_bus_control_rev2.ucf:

# Copyright (C) 2016-2017, Stephen J. Leary
# All rights reserved.
#
# This file is part of TF530 (Terrible Fire 030 Accelerator)
#
# TF530 is free software: you can redistribute it and/or modify
# it under the terms of the GNU General Public License as published by
# the Free Software Foundation, either version 3 of the License, or
# (at your option) any later version.
#
# TF530 is distributed in the hope that it will be useful,
# but WITHOUT ANY WARRANTY; without even the implied warranty of
# MERCHANTABILITY or FITNESS FOR A PARTICULAR PURPOSE.  See the
# GNU General Public License for more details.
#
# You should have received a copy of the GNU General Public License
# along with TF530. If not, see <http://www.gnu.org/licenses/>.

#Clocks
NET "CLKCPU"		LOC="16";
NET "CLKCPU" BUFG=CLK;
NET "CLKCPU" TNM_NET = "CLKCPU"; # gives the net clk a group name as CLKCPU
TIMESPEC "TS_CLKCPU" = PERIOD "CLKCPU" 20 ns ; # add 20 ns PERIOD constraint the
OFFSET = IN 5 ns BEFORE "CLKCPU" ; # add  offset in constraint
OFFSET = OUT 5 ns AFTER "CLKCPU" ; # add  offset out constraint

NET "CLK7M"		LOC="15";
NET "CLK7M" BUFG=CLK;
NET "CLK7M" TNM_NET = "CLK7M"; # gives the net clk a group name as CLK7M
TIMESPEC "TS_CLK7M" = PERIOD "CLK7M" 139 ns ; # add 139 ns PERIOD constraint the
OFFSET = IN 15 ns BEFORE "CLK7M" ; # add  offset in constraint
OFFSET = OUT 15 ns AFTER "CLK7M" ; # add  offset out constraint

NET "A0"      LOC="39";
NET "A<12>"      LOC="42";
NET "A<13>"      LOC="43";
NET "A<14>"      LOC="40";
NET "A<15>"      LOC="44";
NET "A<16>"      LOC="45";
NET "A<17>"      LOC="46";
NET "A<18>"      LOC="47";
NET "A<19>"      LOC="48";
NET "A<20>"      LOC="49";
NET "A<21>"      LOC="50";
NET "A<22>"      LOC="51";
NET "A<23>"      LOC="52";
NET "AS"      LOC="6";
NET "AS20"      LOC="23";
#NET "AUX<0>"      LOC="58";
#NET "AUX<1>"      LOC="57";
NET "AVEC"      LOC="35";
NET "BERR"      LOC="27";
NET "BG"      LOC="11";
NET "BG20"      LOC="32";
NET "BGACK"      LOC="12";
NET "CPCS"      LOC="62";
NET "CPSENSE"      LOC="20";
NET "DS20"      LOC="24";
NET "DSACK<0>"      LOC="63";
NET "DSACK<1>"      LOC="64";
NET "DTACK"      LOC="10";
NET "E"      LOC="22";
NET "FC<0>"      LOC="34";
NET "FC<1>"      LOC="33";
NET "FC<2>"      LOC="31";
#NET "HALT"      LOC="17";
NET "IDECS<0>"      LOC="1";
NET "IDECS<1>"      LOC="61";
NET "IDEWAIT"      LOC="2";
#NET "INT2"      LOC="60";
NET "INTSIG"      LOC="59";
NET "IOR"      LOC="5";
NET "IOW"      LOC="4";
NET "LDS"      LOC="8";
NET "OVR"      LOC="56";
NET "RW00"      LOC="9";
NET "RW20"      LOC="13";
#NET "RESET"      LOC="18";
NET "SIZ<0>"      LOC="36";
NET "SIZ<1>"      LOC="38";
NET "UDS"      LOC="7";
NET "VMA"      LOC="19";
NET "VPA"      LOC="25";

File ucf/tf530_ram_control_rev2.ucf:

# Copyright (C) 2016-2017, Stephen J. Leary
# All rights reserved.
#
# This file is part of TF530 (Terrible Fire 030 Accelerator)
#
# TF530 is free software: you can redistribute it and/or modify
# it under the terms of the GNU General Public License as published by
# the Free Software Foundation, either version 3 of the License, or
# (at your option) any later version.
#
# TF530 is distributed in the hope that it will be useful,
# but WITHOUT ANY WARRANTY; without even the implied warranty of
# MERCHANTABILITY or FITNESS FOR A PARTICULAR PURPOSE.  See the
# GNU General Public License for more details.
#
# You should have received a copy of the GNU General Public License
# along with TF530. If not, see <http://www.gnu.org/licenses/>.

#Clocks
NET "CLKCPU"		LOC="16";
NET "CLKCPU" BUFG=CLK;
NET "CLKCPU" TNM_NET = "CLKCPU"; # gives the net clk a group name as CLKCPU
TIMESPEC "TS_CLKCPU" = PERIOD "CLKCPU" 20 ns ; # add 20 ns PERIOD constraint the
OFFSET = IN 5 ns BEFORE "CLKCPU" ; # add  offset in constraint
OFFSET = OUT 5 ns AFTER "CLKCPU" ; # add  offset out constraint

NET "A0"      LOC="51";
NET "A1"      LOC="4";
NET "AB<2>"      LOC="9";
NET "AB<3>"      LOC="10";
NET "AB<4>"      LOC="11";
NET "AB<5>"      LOC="12";
NET "AB<6>"      LOC="13";
NET "AB<7>"      LOC="36";
NET "A<12>"      LOC="50";
NET "A<13>"      LOC="49";
NET "A<15>"      LOC="38";
NET "A<16>"      LOC="35";
NET "A<17>"      LOC="20";
NET "A<18>"      LOC="19";
NET "A<19>"      LOC="18";
NET "A<20>"      LOC="17";
NET "A<21>"      LOC="2";
NET "A<22>"      LOC="1";
NET "A<23>"      LOC="64";
NET "AS20"      LOC="47";
NET "CBACK"      LOC="48";
NET "CBREQ"      LOC="46";
NET "CIIN"      LOC="44";
NET "D<0>"      LOC="62";
NET "D<1>"      LOC="61";
NET "D<2>"      LOC="58";
NET "D<3>"      LOC="59";
NET "D<4>"      LOC="33";
NET "D<5>"      LOC="32";
NET "D<6>"      LOC="31";
NET "D<7>"      LOC="34";
NET "DS20"      LOC="45";
NET "IDEINT"      LOC="57";
NET "IDEWAIT"      LOC="52";
NET "INT2"      LOC="63";
NET "INTCYCLE"      LOC="56";
NET "RW20"      LOC="40";
NET "RAMCS<0>"      LOC="27";
NET "RAMCS<1>"      LOC="25";
NET "RAMCS<2>"      LOC="24";
NET "RAMCS<3>"      LOC="23";
NET "RAMOE"      LOC="22";
NET "RESET"      LOC="60";
NET "SIZ<0>"      LOC="42";
NET "SIZ<1>"      LOC="39";
#NET "SPI_CLK"      LOC="15";
#NET "SPI_CS<0>"      LOC="7";
#NET "SPI_CS<1>"      LOC="8";
#NET "SPI_MISO"      LOC="6";
#NET "SPI_MOSI"      LOC="5";
NET "STERM"      LOC="43";

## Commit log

2017-03-12 final version
2017-03-12 images

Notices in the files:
eagle/SL530.brd:
(C) 2016 S.J Leary
Published under the
GNU Public License (GPL) v2
parts and their libraries:
microbuilder: This work is placed in the public domain, and may be freely used for commercial and non-commercial work with the following conditions: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
SparkFun-Retired: Licensing:Creative Commons ShareAlike 4.0 International - https://creativecommons.org/licenses/by-sa/4.0
